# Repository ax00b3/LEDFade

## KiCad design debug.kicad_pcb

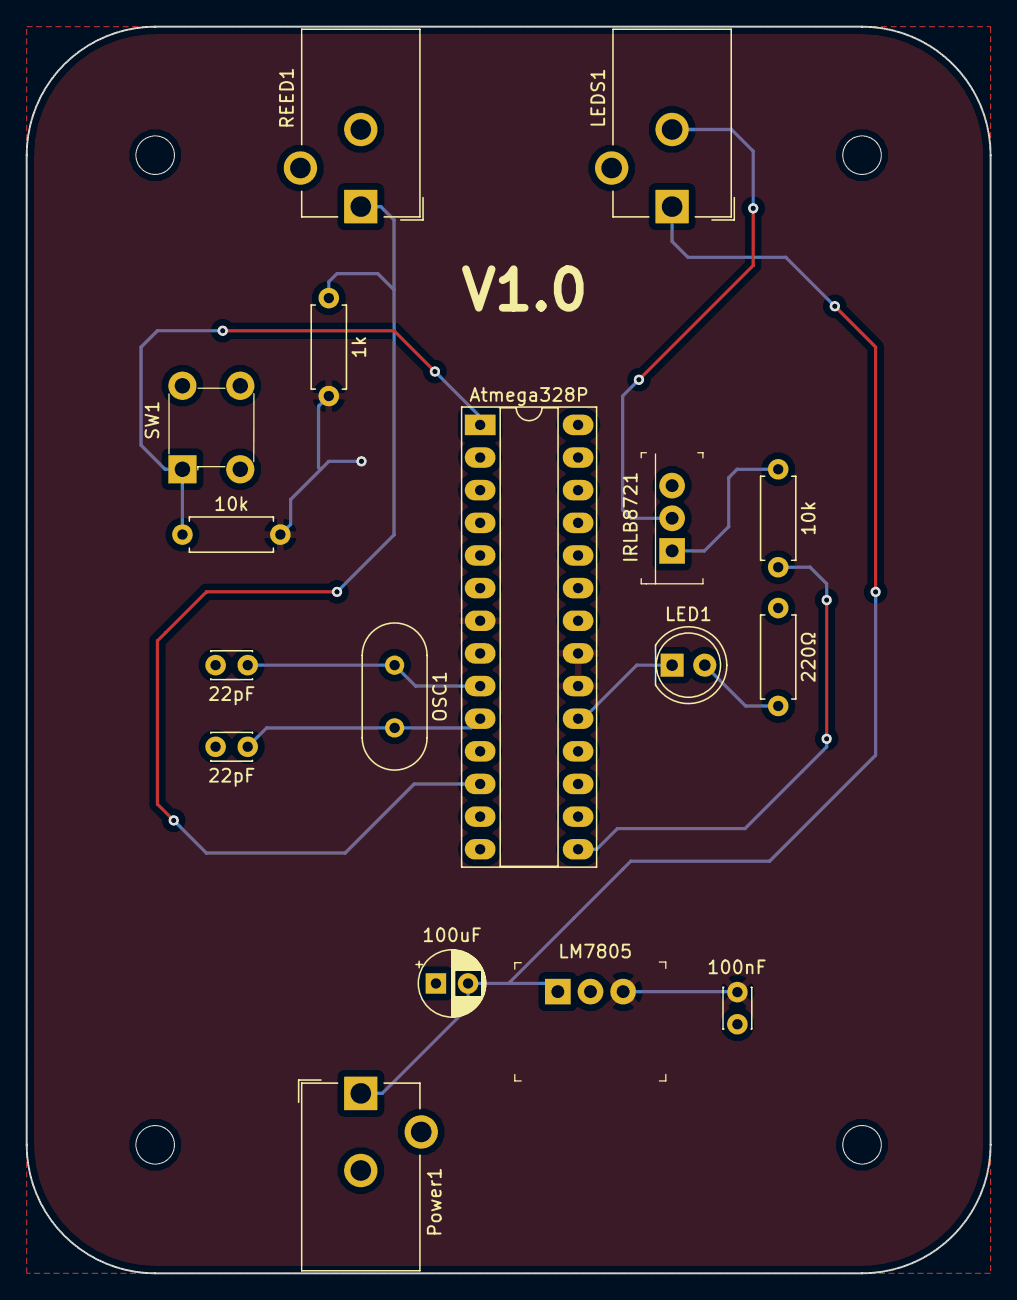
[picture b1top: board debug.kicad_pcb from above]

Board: 2 copper layers, 75.0 x 97.0 mm, 17 parts (0 on the bottom side), 12 nets.

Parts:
1k: 1k; R_Axial_DIN0207_L6.3mm_D2.5mm_P7.62mm_Horizontal
10k, 10k#2: 10k; R_Axial_DIN0207_L6.3mm_D2.5mm_P7.62mm_Horizontal
22pF, 22pF#2: 22pF; C_Disc_D3.0mm_W2.0mm_P2.50mm
100nF: 100nF; C_Disc_D3.0mm_W2.0mm_P2.50mm
100uF: 100uF; CP_Radial_D5.0mm_P2.50mm
220Ω: 220Ω; R_Axial_DIN0207_L6.3mm_D2.5mm_P7.62mm_Horizontal
Atmega328P: ATMEGA328P-PDIP; DIP-28_W7.62mm_Socket_LongPads
IRLB8721: IRLB8721PBF; TO-220-3
LED1: LED; LED_D5.0mm
LEDS1: Barrel_Jack; BarrelJack_CUI_PJ-102AH_Horizontal
LM7805: V7805-1000; 3-SIP_Module_V7805-1000
OSC1: Crystal_Small; Crystal_HC49-4H_Vertical
Power1: Barrel_Jack; BarrelJack_CUI_PJ-102AH_Horizontal
REED1: SW_Reed; BarrelJack_CUI_PJ-102AH_Horizontal
SW1: SW_SPST; Switch_Tactile_THT_6x6mm

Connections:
+5V: 1k.2, 10k.2, 100nF.2, Atmega328P.7, Atmega328P.20, Atmega328P.21, LM7805.3
+12V: 100uF.2, LEDS1.1, LM7805.1, Power1.1
/PWM: 10k#2.2, Atmega328P.15
GND: 22pF.2, 22pF#2.2, 100nF.1, 100uF.1, 220Ω.1, Atmega328P.8, Atmega328P.22, IRLB8721.3, LM7805.2, Power1.2, REED1.2, SW1.2
unnamed: 22pF.1, Atmega328P.9, OSC1.1
unnamed: 22pF#2.1, Atmega328P.10, OSC1.2
unnamed: Atmega328P.19, LED1.1
unnamed: 220Ω.2, LED1.2
unnamed: 10k.1, Atmega328P.1, SW1.1
unnamed: 1k.1, Atmega328P.12, REED1.1
unnamed: IRLB8721.2, LEDS1.2
unnamed: 10k#2.1, IRLB8721.1

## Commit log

2018-12-17 added sketch
2018-12-17 added images
2018-12-17 added board pics
